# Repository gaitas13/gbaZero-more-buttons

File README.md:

This board is not a board of honor... no highly esteemed board is commemorated here... nothing valued is here.

I have no experience with pcb so no idea wheter this is an electrical hazard or not, i haven't tried it myself, nor i have the board yet

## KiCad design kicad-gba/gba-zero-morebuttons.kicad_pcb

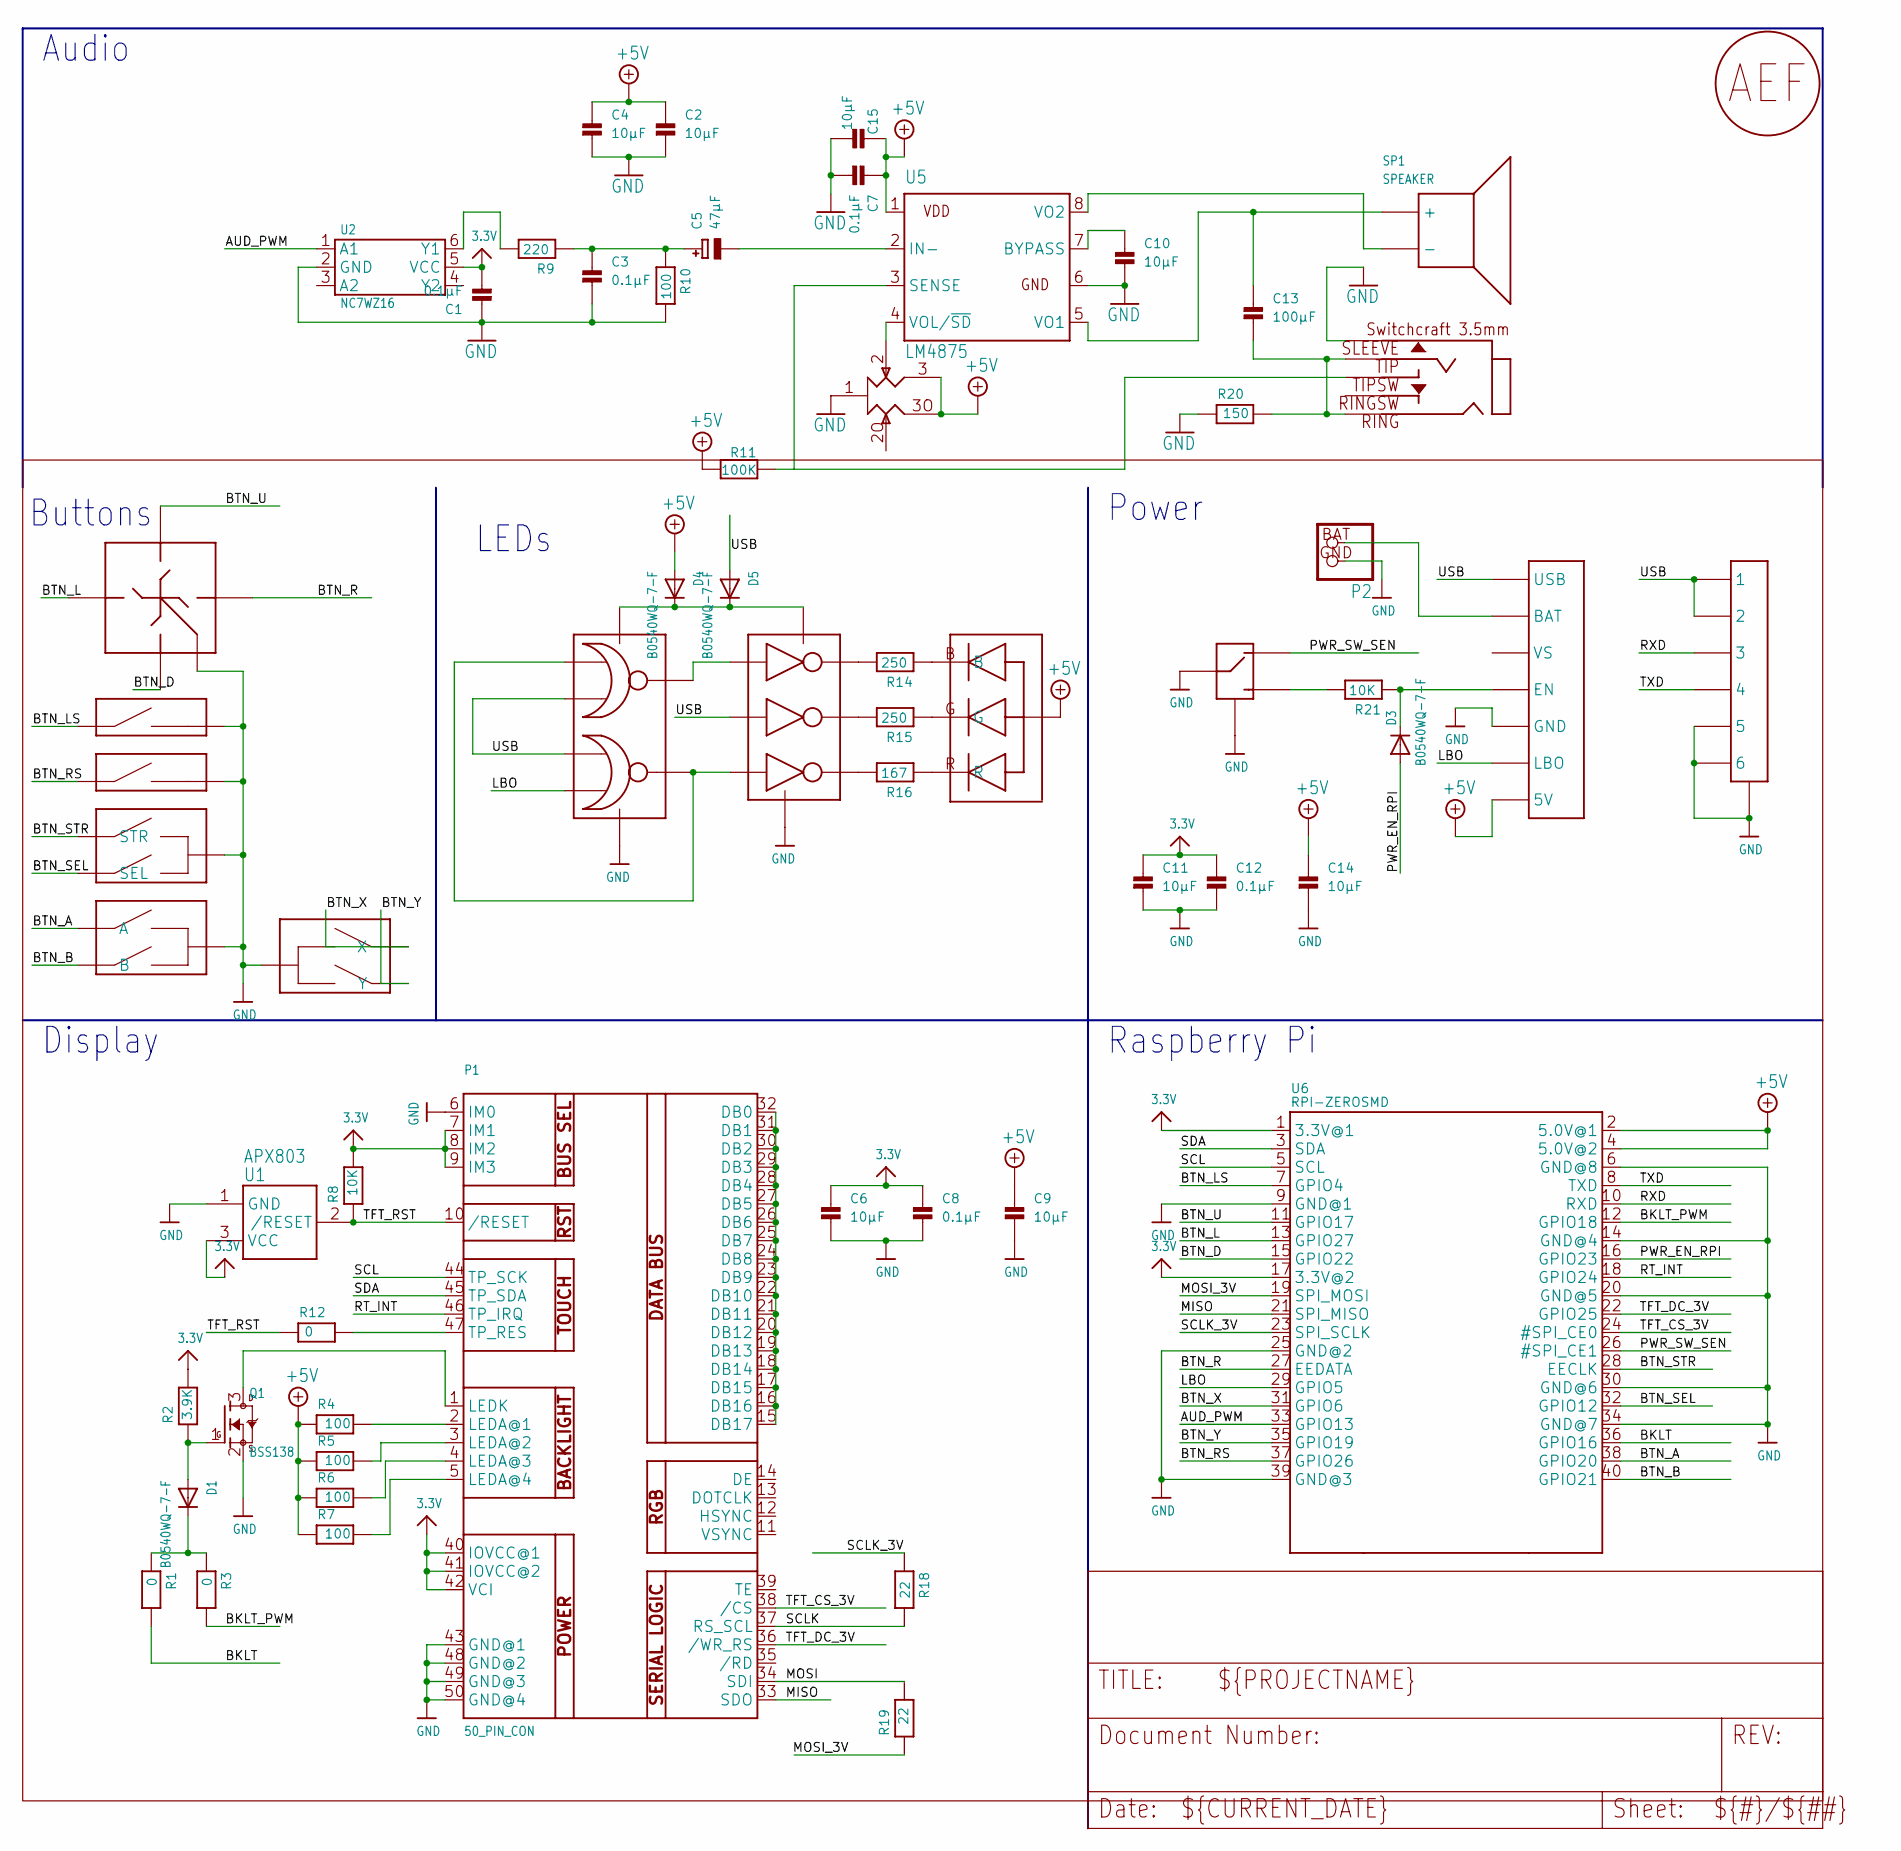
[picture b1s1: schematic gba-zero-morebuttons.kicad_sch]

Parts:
C1, C3, C7, C8, C12: 0.1μF; 0603
C2, C4, C6, C9, C10, C11, C14, C15: 10μF; 0603
C5: 47μF; EIA6032-28_C-R
C13: 100μF; 1206
D1, D3, D4, D5: B0540WQ-7-F; SOD-123
D2: LTST-C19HE1WT; WL-SBCW-0606
J1: SWTCHCRFT_3.5JACK5-JACK-SMD; 4-JACK-SMD
P1: 50_PIN_CON; FPC-50-CON
P2: JST_2PIN; JSTPH2
P3: LINK_CONNECTOR
Q1: BSS138; SOT23-WIDE
R1, R3, R12: 0; 0603
R2: 3.9K; 0603
R4, R5, R6, R7, R10: 100; 0603
R8, R21: 10K; 0603
R9: 220; 0603
R11: 100K; 0603
R14, R15: 250; 0603
R16: 167; 0603
R17: 10K; RK10J12E0A0A
R18, R19: 22; 0603
R20: 150; 0603
S1: D-PAD
S2, S3: SHOULDER_BUTTON
S4: START_SELECT_BUTTON
S5: AB_BUTTON
S6: PWR_SWITCH; PWR-SWITCH
S7: XY_BUTTON
SP1: SPEAKER
U1: APX803; SOT23
U2: NC7WZ16; SC-70-6
U3: 74LVC2G02; TSSOP-8
U4: 74LVC3G04; TSSOP-8
U5: LM4875; SO-8
U6: RPI-ZEROSMD; RPI-SMD
U7: POWERBOOST-1000C
U$1: SIGNATURE

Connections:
3.3V: C1.2, C6.1, C8.1, C11.1, C12.1, P1.7 (IM1), P1.8 (IM2), P1.9 (IM3), P1.40 (IOVCC@1), P1.41 (IOVCC@2), P1.42 (VCI), R2.2, R8.2, U1.3 (VCC), U2.5 (VCC), U6.1 (3.3V@1), U6.17 (3.3V@2)
+5V: C2.1, C4.1, C7.1, C9.1, C14.1, C15.1, D2.VCC, D4.A, R4.1, R5.1, R6.1, R7.1, R11.2, R17.3, R17.3O, U5.1 (VDD), U6.2 (5.0V@1), U6.4 (5.0V@2), U7.5V
/AUD_PWM: U2.1 (A1), U6.33 (GPIO13)
/BKLT: R1.2, U6.36 (GPIO16)
/BKLT_PWM: R3.2, U6.12 (GPIO18)
/BTN_A: S5.A@1 (A), S5.A@2 (A), U6.38 (GPIO20)
/BTN_B: S5.B@1 (B), S5.B@2 (B), U6.40 (GPIO21)
/BTN_D: S1.DOWN, U6.15 (GPIO22)
/BTN_L: S1.LEFT, U6.13 (GPIO27)
/BTN_LS: S2.SW (1), U6.7 (GPIO4)
/BTN_R: S1.RIGHT, U6.27 (EEDATA)
/BTN_RS: S3.SW (1), U6.37 (GPIO26)
/BTN_SEL: S4.SEL, U6.32 (GPIO12)
/BTN_STR: S4.STR, U6.28 (EECLK)
/BTN_U: S1.UP, U6.11 (GPIO17)
/BTN_X: S7.X@1 (X), S7.X@2 (X), U6.31 (GPIO6)
/BTN_Y: S7.Y@1 (Y), S7.Y@2 (Y), U6.35 (GPIO19)
/LBO: U3.6 (2B), U6.29 (GPIO5), U7.LBO
/MISO: P1.33 (SDO), U6.21 (SPI_MISO)
/MOSI: P1.34 (SDI), R19.2
/MOSI_3V: R19.1, U6.19 (SPI_MOSI)
/PWR_EN_RPI: D3.A, U6.16 (GPIO23)
/PWR_SW_SEN: S6.L, U6.26 (#SPI_CE1)
/RT_INT: P1.46 (TP_IRQ), U6.18 (GPIO24)
/RXD: P3.3, U6.10 (RXD)
/SCL: P1.44 (TP_SCK), U6.5 (SCL)
/SCLK: P1.37 (RS_SCL), R18.2
/SCLK_3V: R18.1, U6.23 (SPI_SCLK)
/SDA: P1.45 (TP_SDA), U6.3 (SDA)
/TFT_CS_3V: P1.38 (/CS), U6.24 (#SPI_CE0)
/TFT_DC_3V: P1.36 (/WR_RS), U6.22 (GPIO25)
/TFT_RST: P1.10 (/RESET), R8.1, R12.1, U1.2 (/RESET)
/TXD: P3.4, U6.8 (TXD)
/USB: D5.A, P3.1, P3.2, U3.2 (1B), U3.5 (2A), U4.3 (2A), U7.USB
GND: C1.1, C2.2, C3.2, C4.2, C6.2, C7.2, C8.2, C9.2, C10.2, C11.2, C12.2, C14.2, C15.2, J1.1, P1.6 (IM0), P1.43 (GND@1), P1.48 (GND@2), P1.49 (GND@3), P1.50 (GND@4), P2.GND (1), P3.5, P3.6, P3.GND@1 (GND), P3.GND@2 (GND), Q1.2 (S), R10.2, R17.1, R20.1, S1.GND@1 (GND), S1.GND@2 (GND), S1.GND@3 (GND), S1.GND@4 (GND), S2.GND@1 (2), S2.GND@2 (2), S2.GND@3 (2), S3.GND@1 (2), S3.GND@2 (2), S3.GND@3 (2), S4.GND@1 (GND), S4.GND@2 (GND), S4.GND@3 (GND), S4.GND@4 (GND), S5.GND@1 (GND), S5.GND@2 (GND), S5.GND@3 (GND), S5.GND@4 (GND), S6.C@1 (C), S6.C@2 (C), S6.GND@1 (GND), S6.GND@2 (GND), S7.GND@1 (GND), S7.GND@2 (GND), S7.GND@3 (GND), S7.GND@4 (GND), U1.1 (GND), U2.2 (GND), U3.4 (GND), U4.4 (GND), U5.6 (GND@), U6.6 (GND@8), U6.9 (GND@1), U6.14 (GND@4), U6.20 (GND@5), U6.25 (GND@2), U6.30 (GND@6), U6.34 (GND@7), U6.39 (GND@3), U7.GND@1 (GND), U7.GND@2 (GND)
unnamed: C3.1, C5.+, R9.1, R10.1
unnamed: C10.1, U5.7 (BYPASS)
unnamed: C13.1, SP1.1 (+), U5.5 (VO1)
unnamed: C13.2, J1.2, J1.3, R20.2
unnamed: D1.C, R1.1, R3.1
unnamed: D2.B, R14.1
unnamed: D2.G, R15.1
unnamed: D2.R, R16.1
unnamed: D3.C, R21.1, U7.EN
unnamed: P1.15 (DB17), P1.16 (DB16), P1.17 (DB15), P1.18 (DB14), P1.19 (DB13), P1.20 (DB12), P1.21 (DB11), P1.22 (DB10), P1.23 (DB9), P1.24 (DB8), P1.25 (DB7), P1.26 (DB6), P1.27 (DB5), P1.28 (DB4), P1.29 (DB3), P1.30 (DB2), P1.31 (DB1), P1.32 (DB0)
unnamed: P1.2 (LEDA@1), R4.2
unnamed: P1.3 (LEDA@2), R5.2
unnamed: P1.4 (LEDA@3), R6.2
unnamed: P1.5 (LEDA@4), R7.2
unnamed: P1.1 (LEDK), Q1.3 (D)
unnamed: P1.47 (TP_RES), R12.2
unnamed: P2.BAT (2), U7.BAT
unnamed: D1.A, Q1.1 (G), R2.1
unnamed: R21.2, S6.R
unnamed: SP1.2 (-), U5.8 (VO2)
unnamed: R9.2, U2.6 (Y1)
unnamed: U3.1 (1A), U3.3 (2Y), U4.6 (3A)
unnamed: U3.7 (1Y), U4.1 (1A)
unnamed: D4.C, D5.C, U3.8 (VCC), U4.8 (VCC)
unnamed: R14.2, U4.7 (1Y)
unnamed: R15.2, U4.5 (2Y)
unnamed: R16.2, U4.2 (3Y)
unnamed: C5.-, U5.2 (IN-)
unnamed: J1.5, R11.1, U5.3 (SENSE)
unnamed: R17.2, U5.4 (VOL/~SD)

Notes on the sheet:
Raspberry Pi
Power
Buttons
Display
LEDs
Audio

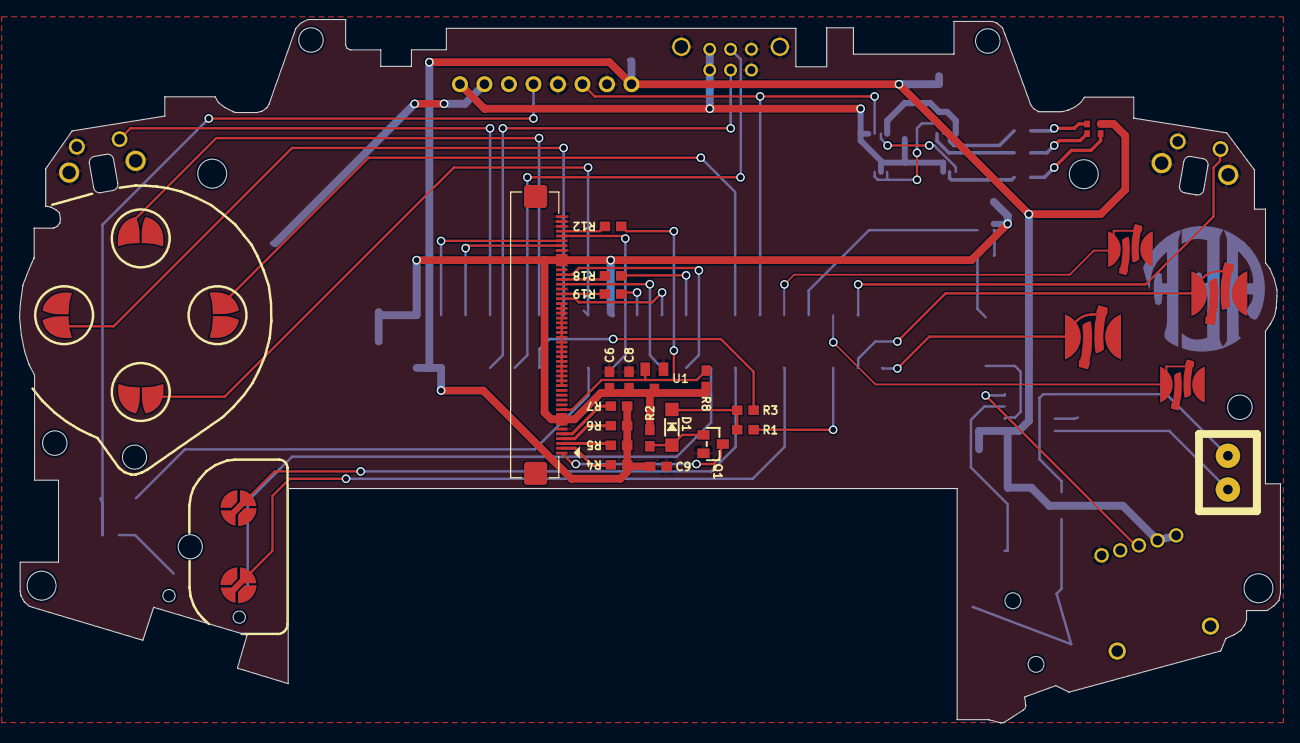
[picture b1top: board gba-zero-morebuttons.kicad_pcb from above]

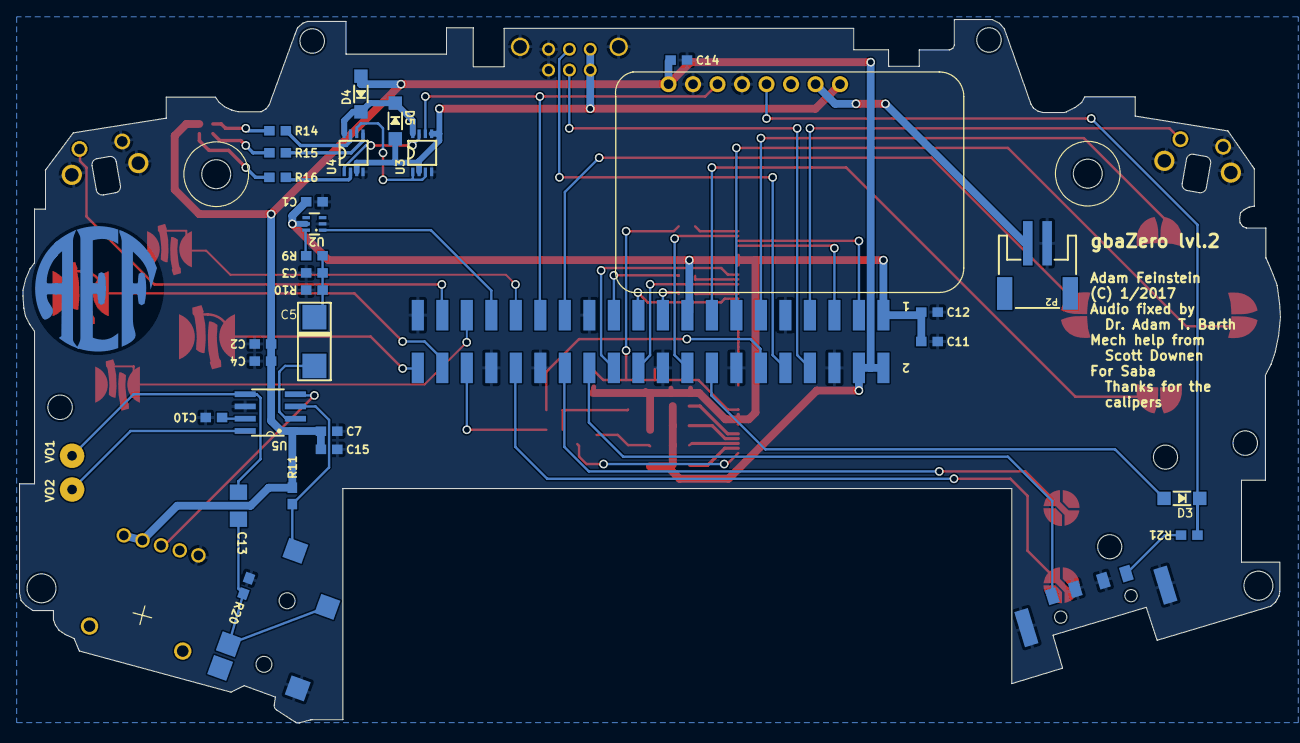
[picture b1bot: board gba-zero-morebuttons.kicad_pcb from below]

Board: 2 copper layers, 130.7 x 72.9 mm, 71 parts (34 on the bottom side), 65 nets.

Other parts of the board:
UNK_HOLE_0: dummyfp0
UNK_HOLE_1: dummyfp1
UNK_HOLE_2: dummyfp2
UNK_HOLE_3: dummyfp3
UNK_HOLE_4: dummyfp4
UNK_HOLE_5: dummyfp5
UNK_HOLE_6: dummyfp6
UNK_HOLE_7: dummyfp7
UNK_HOLE_10: dummyfp10
UNK_HOLE_11: dummyfp11

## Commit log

2026-01-03 Create README.md warning about the board
2026-01-03 added kicad files
2026-01-04 fixed major issue
2026-01-05 final update of button position
